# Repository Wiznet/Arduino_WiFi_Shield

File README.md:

# Wi-Fi Shield for Arduino using [WizFi210](http://www.wiznet.co.kr/WizFi210) from [Wiznet](http://www.wiznet.co.kr/)

## Hardware
These are PCB files for the WizFi Shield for Arduino. The files were created in the free & low cost EagleCad software available form [here](http://www.cadsoftusa.com/download-eagle/?language=en).

## Software
These are driver code of WizFi shield and test code.
For Arduino library source code, refer to https://github.com/Wiznet/WizFiShield

## Documents
Manual for WizFi shield

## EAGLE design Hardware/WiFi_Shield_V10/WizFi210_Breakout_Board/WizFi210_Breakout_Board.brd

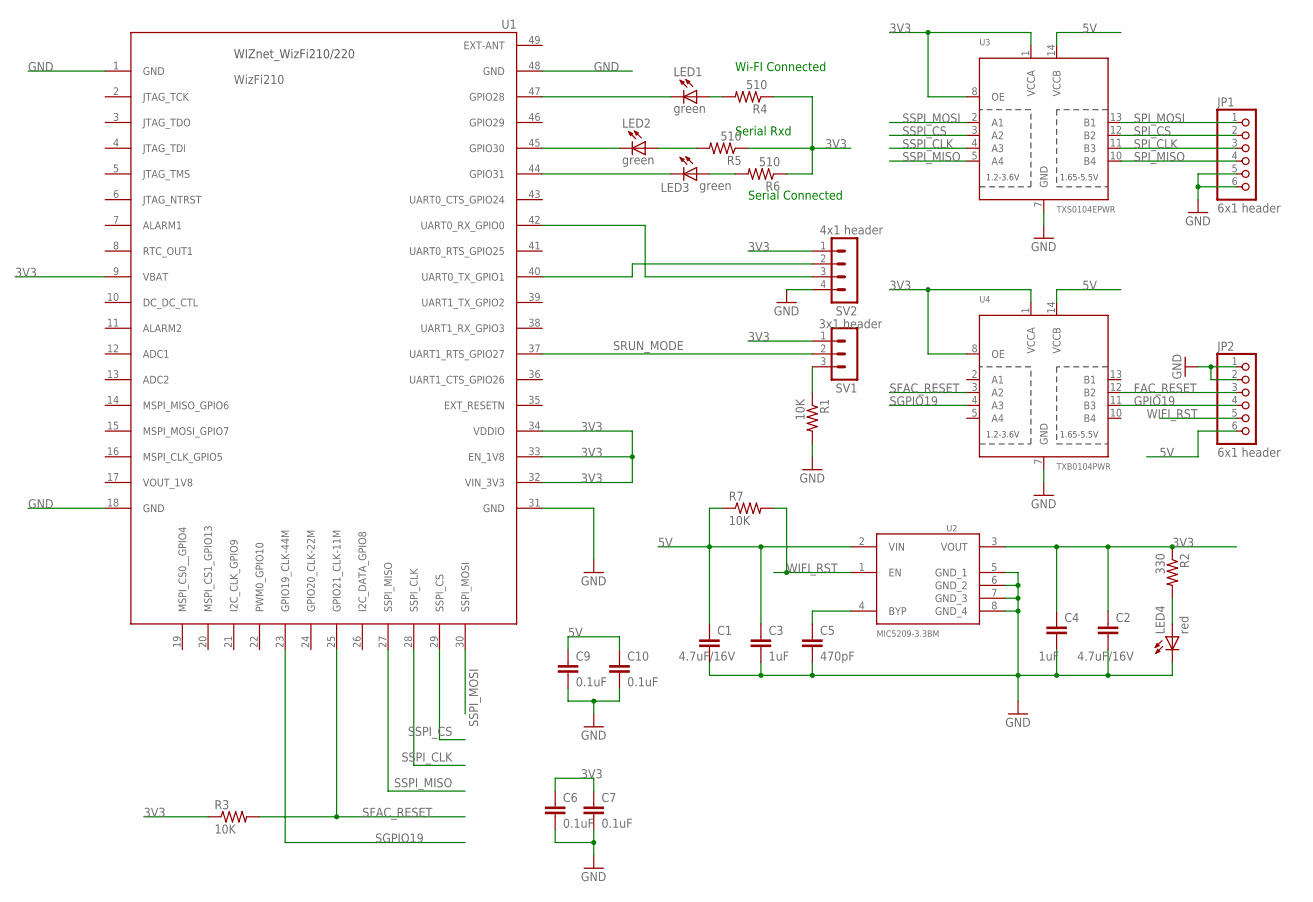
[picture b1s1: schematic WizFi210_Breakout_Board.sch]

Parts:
C1: 4.7uF/16V; C0805
C2: 4.7uF/16V; C0603
C3: 1uF; C0603
C4: 1uF; C0805
C5: 470pF; C0603
C6, C7, C9, C10: 0.1uF; C0603
JP1, JP2: 6x1 header; 1X06
LED1, LED2, LED3: green; CHIP-LED0805
LED4: red; CHIP-LED0805
R1, R3, R7: 10K; 0603-RES
R2: 330; 0603-RES
R4, R5, R6: 510; 0603-RES
SV1: 3x1 header; MA03-1
SV2: 4x1 header; MA04-1
U1: WizFi210; WIZFI210/220
U2: MIC5209-3.3BM; SO08
U3: TXS0104EPWR; TSSOP14
U4: TXB0104PWR; TSSOP14

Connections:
3V3: C2.1, C4.1, C6.1, C7.1, R2.1, R3.1, R4.1, R5.1, R6.1, SV1.1, SV2.1, U1.9 (VBAT), U1.32 (VIN_3V3), U1.33 (EN_1V8), U1.34 (VDDIO), U2.3 (VOUT), U3.1 (VCCA), U3.8 (OE), U4.1 (VCCA), U4.8 (OE)
5V: C1.1, C3.1, C9.1, C10.1, JP2.6, R7.1, U2.2 (VIN), U3.14 (VCCB), U4.14 (VCCB)
FAC_RESET: JP2.3, U4.12 (B2)
GND: C1.2, C2.2, C3.2, C4.2, C5.2, C6.2, C7.2, C9.2, C10.2, JP1.5, JP1.6, JP2.1, JP2.2, LED4.C, R1.2, SV2.4, U1.1 (GND), U1.18 (GND), U1.31 (GND), U1.48 (GND), U2.5 (GND_1), U2.6 (GND_2), U2.7 (GND_3), U2.8 (GND_4), U3.7 (GND), U4.7 (GND)
GPIO19: JP2.4, U4.11 (B3)
GPIO28: LED1.C, U1.47 (GPIO28)
GPIO30: LED2.C, U1.45 (GPIO30)
GPIO31: LED3.C, U1.44 (GPIO31)
unnamed: R1.1, SV1.3
unnamed: LED4.A, R2.2
unnamed: C5.1, U2.4 (BYP)
unnamed: LED1.A, R4.2
unnamed: LED2.A, R5.2
unnamed: LED3.A, R6.2
SFAC_RESET: R3.2, U1.25 (GPIO21_CLK-11M), U4.3 (A2)
SGPIO19: U1.23 (GPIO19_CLK-44M), U4.4 (A3)
SPI_CLK: JP1.3, U3.11 (B3)
SPI_CS: JP1.2, U3.12 (B2)
SPI_MISO: JP1.4, U3.10 (B4)
SPI_MOSI: JP1.1, U3.13 (B1)
SRUN_MODE: SV1.2, U1.37 (UART1_RTS_GPIO27)
SSPI_CLK: U1.28 (SSPI_CLK), U3.4 (A3)
SSPI_CS: U1.29 (SSPI_CS), U3.3 (A2)
SSPI_MISO: U1.27 (SSPI_MISO), U3.5 (A4)
SSPI_MOSI: U1.30 (SSPI_MOSI), U3.2 (A1)
UART0_RX: SV2.3, U1.42 (UART0_RX_GPIO0)
UART0_TX: SV2.2, U1.40 (UART0_TX_GPIO1)
WIFI_RST: JP2.5, R7.2, U2.1 (EN)

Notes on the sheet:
Wi-FI Connected
Serial Rxd
Serial Connected

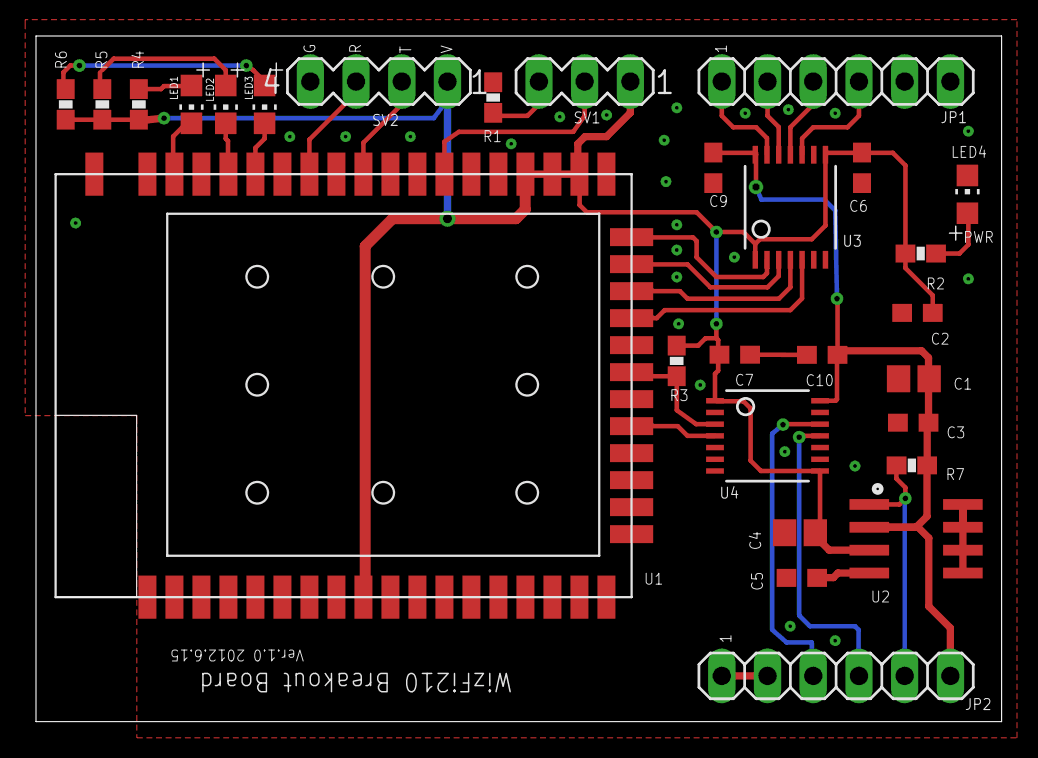
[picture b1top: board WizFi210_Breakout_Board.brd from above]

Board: 2 copper layers, 53.6 x 38.1 mm, 29 parts (1 on the bottom side), 28 nets.

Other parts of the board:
U$1: WIZNET_LOGO_PAC

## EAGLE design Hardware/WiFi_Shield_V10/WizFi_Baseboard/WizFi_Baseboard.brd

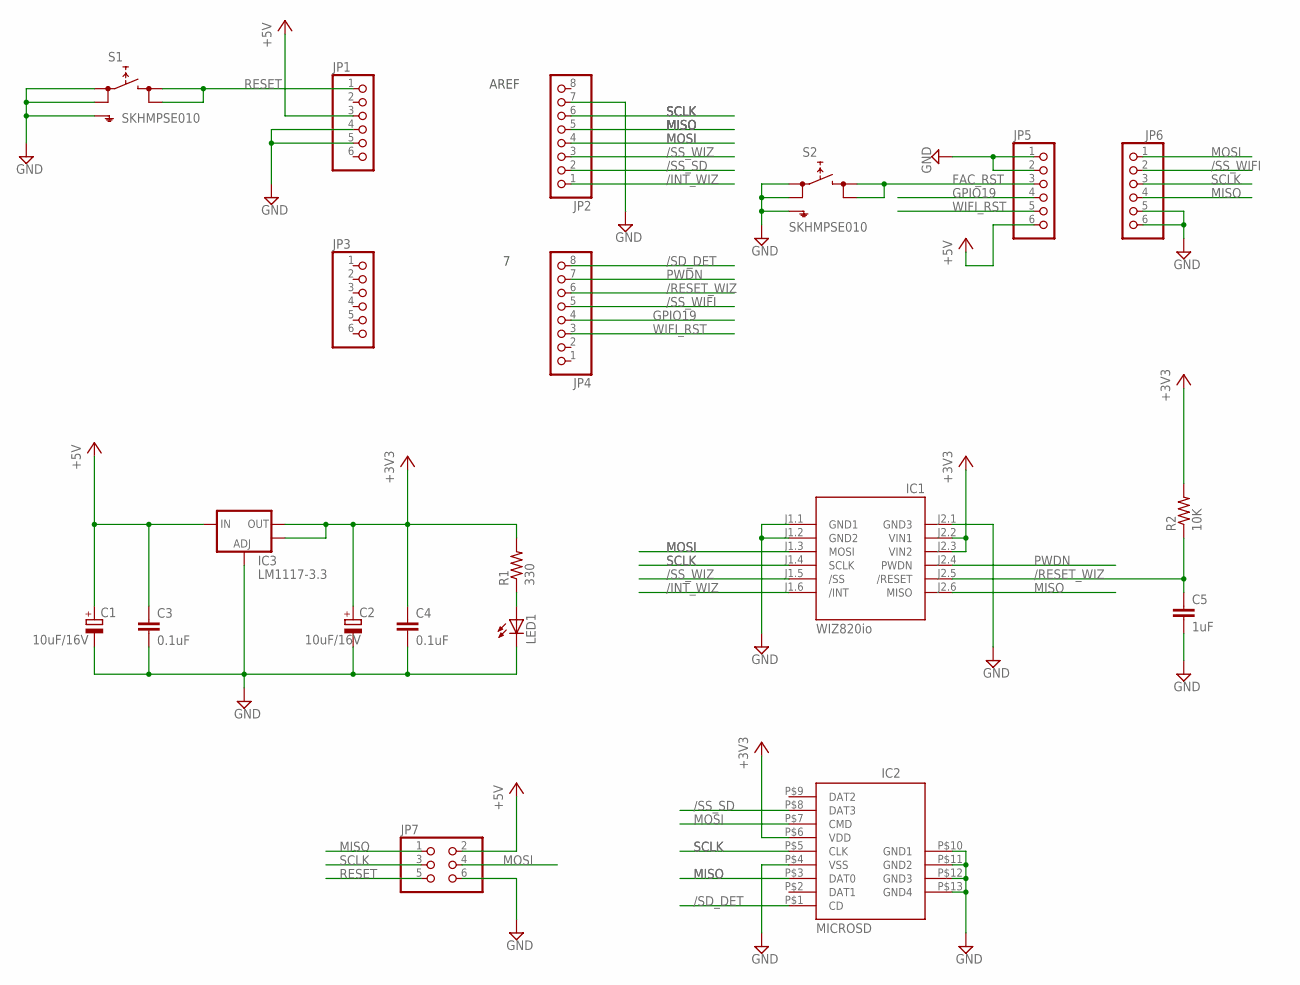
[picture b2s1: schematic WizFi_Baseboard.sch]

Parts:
C1, C2: 10uF/16V; CT3216
C3, C4: 0.1uF; C0805
C5: 1uF; C0805
IC1: WIZ820io; WIZ820IO
IC2: MICROSD; MSDPAC
IC3: LM1117-3.3; SOT223
JP1, JP3, JP5, JP6: PINHD-1X6; 1X06
JP2, JP4: PINHD-1X8; 1X08
JP7: PINHD-2X3; 2X03
LED1: LEDCHIP-LED0805; CHIP-LED0805
R1: 330; R0805
R2: 10K; R0805
S1, S2: SKHMPSE010; SKHMPXE010

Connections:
+3V3: C2.+, C4.1, IC1.J2.2 (VIN1), IC1.J2.3 (VIN2), IC2.P$6 (VDD), IC3.2 (OUT), IC3.4 (OUT), R1.2, R2.2
+5V: C1.+, C3.1, IC3.3 (IN), JP1.3, JP5.6, JP7.2
/INT_WIZ: IC1.J1.6 (/INT), JP2.1
/RESET_WIZ: C5.1, IC1.J2.5 (/RESET), JP4.6, R2.1
/SD_DET: IC2.P$1 (CD), JP4.8
/SS_SD: IC2.P$8 (DAT3), JP2.2
/SS_WIFI: JP4.5, JP6.2
/SS_WIZ: IC1.J1.5 (/SS), JP2.3
FAC_RST: JP5.3, S2.3 (2.1), S2.4 (2.2)
GND: C1.-, C2.-, C3.2, C4.2, C5.2, IC1.J1.1 (GND1), IC1.J1.2 (GND2), IC1.J2.1 (GND3), IC2.P$4 (VSS), IC2.P$10 (GND1), IC2.P$11 (GND2), IC2.P$12 (GND3), IC2.P$13 (GND4), IC3.1 (ADJ), JP1.4, JP1.5, JP2.7, JP5.1, JP5.2, JP6.5, JP6.6, JP7.6, LED1.C, S1.1 (1.1), S1.2 (1.2), S1.5 (SH), S2.1 (1.1), S2.2 (1.2), S2.5 (SH)
GPIO19: JP4.4, JP5.4
MISO: IC1.J2.6 (MISO), IC2.P$3 (DAT0), JP2.5, JP6.4, JP7.1
MOSI: IC1.J1.3 (MOSI), IC2.P$7 (CMD), JP2.4, JP6.1, JP7.4
unnamed: LED1.A, R1.1
PWDN: IC1.J2.4 (PWDN), JP4.7
RESET: JP1.1, JP7.5, S1.3 (2.1), S1.4 (2.2)
SCLK: IC1.J1.4 (SCLK), IC2.P$5 (CLK), JP2.6, JP6.3, JP7.3
WIFI_RST: JP4.3, JP5.5

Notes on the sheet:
AREF
SCLK
MISO
MOSI

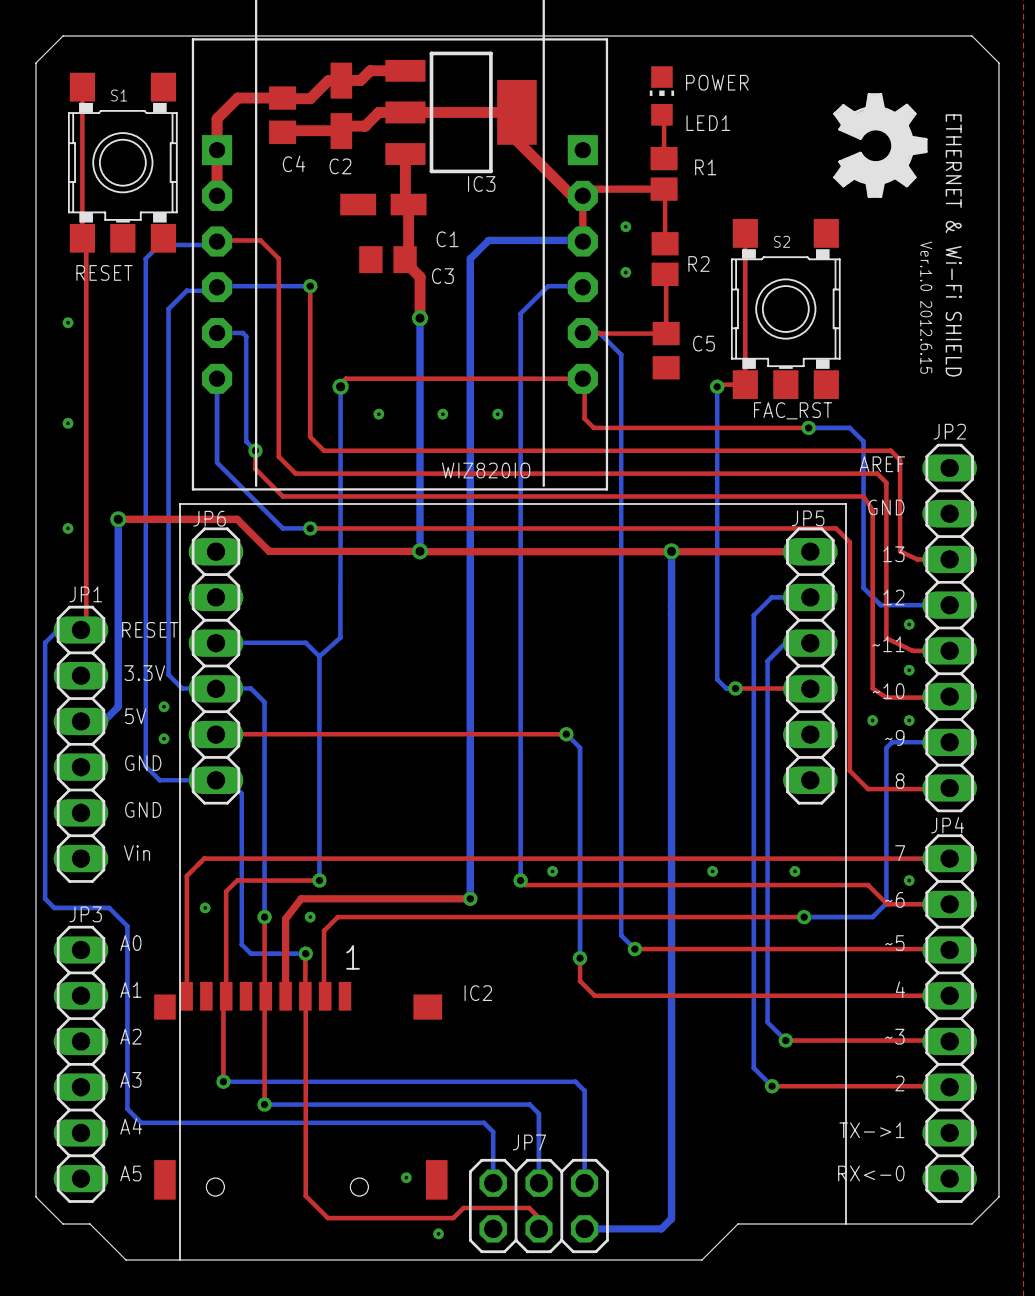
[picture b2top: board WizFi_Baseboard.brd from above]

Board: 2 copper layers, 53.5 x 68.0 mm, 22 parts (1 on the bottom side), 18 nets.

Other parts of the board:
U$1: OSHW_FILLX200_NOTEXT
U$2: WIZNET_LOGO_PAC

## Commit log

2012-07-04 WizFi Shield Hardware Files
2012-07-04 Board image upload
2012-07-04 image removed
2012-08-02 WizFi Shield Test Code and related documents
2012-09-08 PDF schematics update
2013-02-01 Change Readme
    Adding comment for Arduino Lib.
2013-02-01 update txt
2014-03-18 update image

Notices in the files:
parts and their libraries:
SparkFun: Licensing: CC v3.0 Share-Alike You are welcome to use this library for commercial purposes.
